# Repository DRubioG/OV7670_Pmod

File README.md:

# OV7670_Pmod
 This is an adapter for OV7670 to PMOD

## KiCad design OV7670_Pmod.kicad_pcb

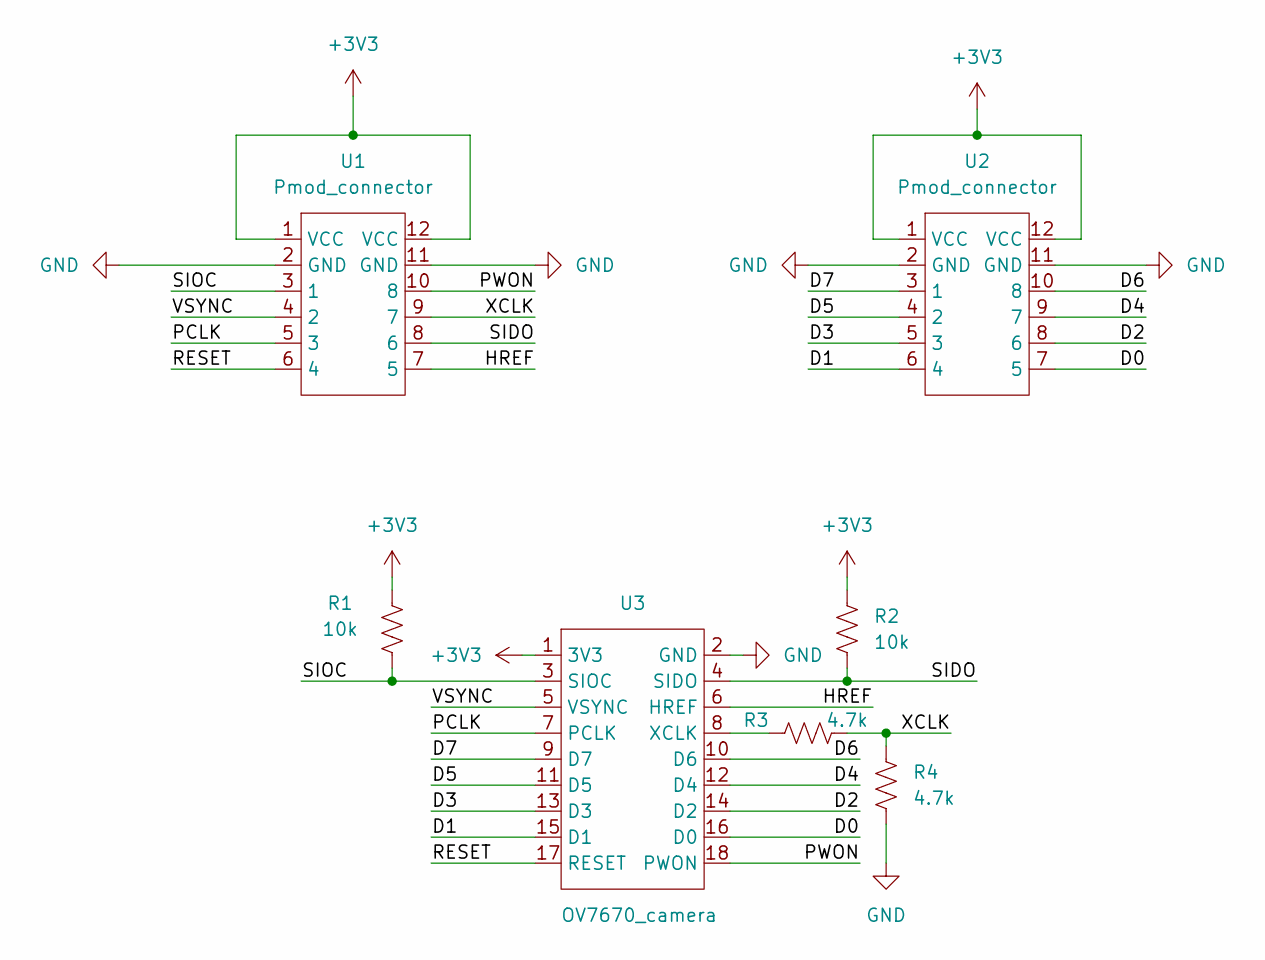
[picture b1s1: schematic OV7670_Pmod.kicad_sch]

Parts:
R1, R2: 10k; R_0805_2012Metric
R3, R4: 4.7k; R_0805_2012Metric
U1, U2: Pmod_connector; PMOD_EXTENSION_BOARD
U3: OV7670_camera

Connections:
+3V3: R1.2, R2.1, U1.1 (VCC), U1.12 (VCC), U2.1 (VCC), U2.12 (VCC), U3.1 (3V3)
/D0: U2.7 (5), U3.16 (D0)
/D1: U2.6 (4), U3.15 (D1)
/D2: U2.8 (6), U3.14 (D2)
/D3: U2.5 (3), U3.13 (D3)
/D4: U2.9 (7), U3.12 (D4)
/D5: U2.4 (2), U3.11 (D5)
/D6: U2.10 (8), U3.10 (D6)
/D7: U2.3 (1), U3.9 (D7)
/HREF: U1.7 (5), U3.6 (HREF)
/PCLK: U1.5 (3), U3.7 (PCLK)
/PWON: U1.10 (8), U3.18 (PWON)
/RESET: U1.6 (4), U3.17 (RESET)
/SIDO: R2.2, U1.8 (6), U3.4 (SIDO)
/SIOC: R1.1, U1.3 (1), U3.3 (SIOC)
/VSYNC: U1.4 (2), U3.5 (VSYNC)
/XCLK: R3.2, R4.1, U1.9 (7)
GND: R4.2, U1.2 (GND), U1.11 (GND), U2.2 (GND), U2.11 (GND), U3.2 (GND)
unnamed: R3.1, U3.8 (XCLK)

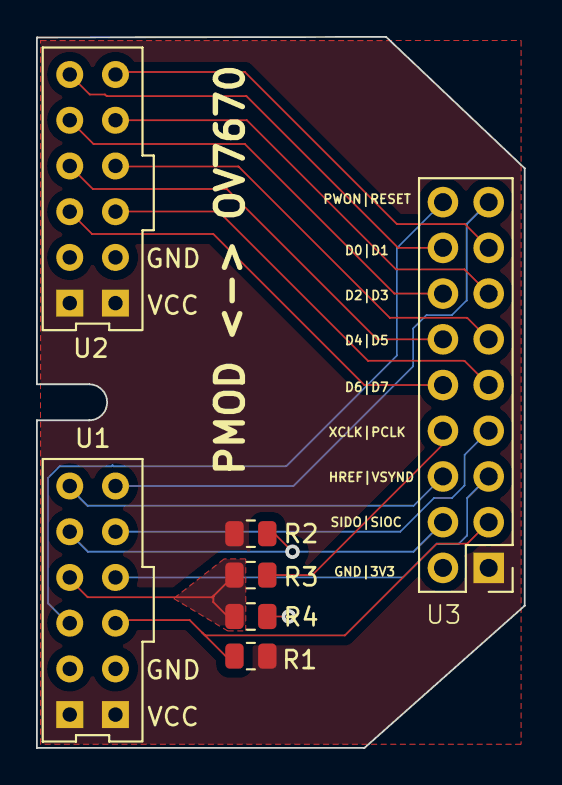
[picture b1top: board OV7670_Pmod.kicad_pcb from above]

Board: 2 copper layers, 27.1 x 39.5 mm, 7 parts (0 on the bottom side), 19 nets.
